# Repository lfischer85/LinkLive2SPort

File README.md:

# LinkLive2SPort
LinkLive to SPort Converter

Contains AVR GCC Files as well as KiCad Files for an Castle Creations LINK LIVE Protocoll to FrSky S.Port Converter.

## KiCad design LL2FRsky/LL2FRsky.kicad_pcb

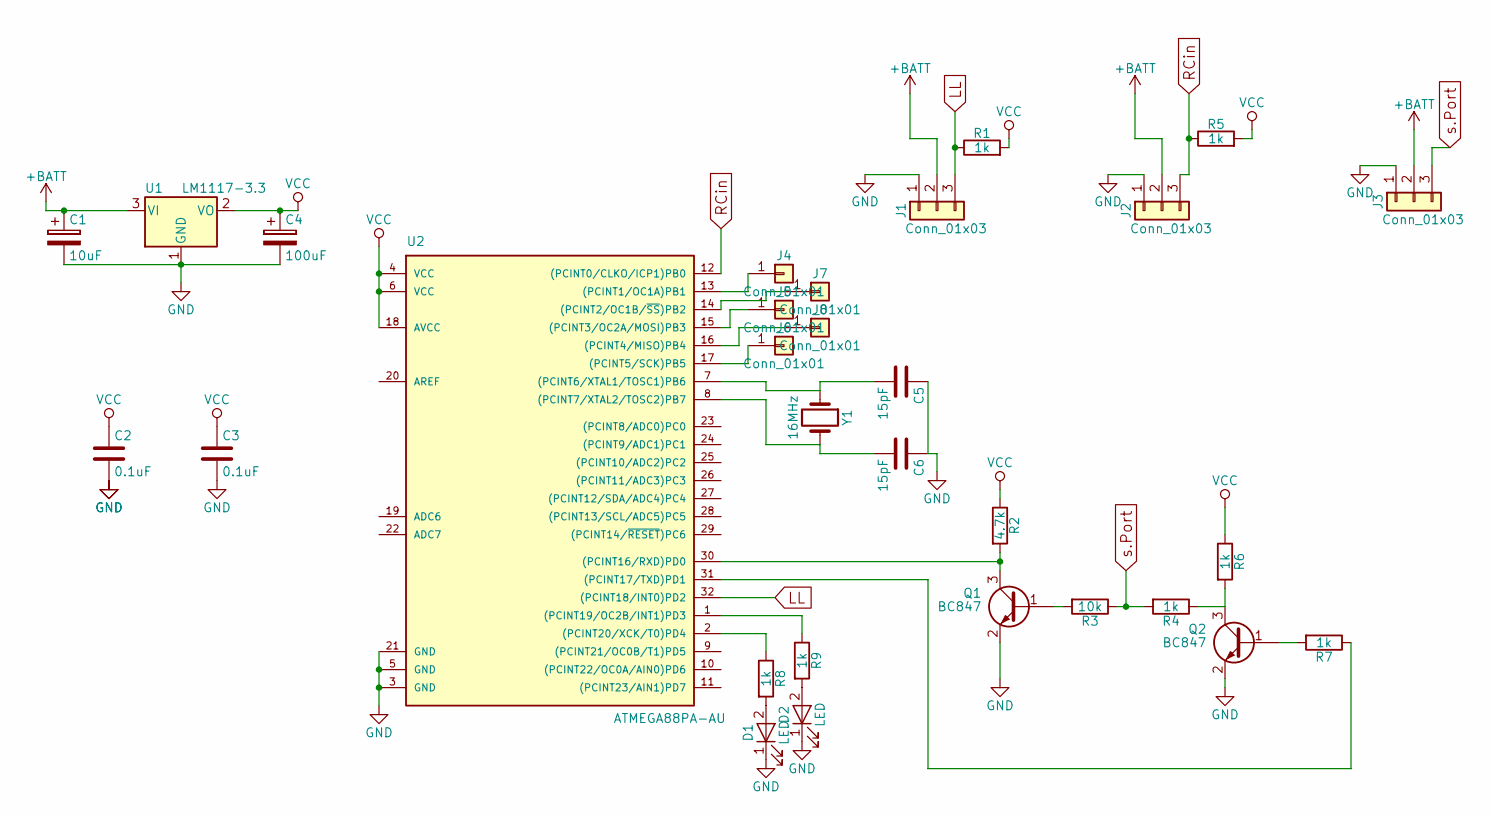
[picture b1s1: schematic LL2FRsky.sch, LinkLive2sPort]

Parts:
C1: 10uF; CP_Tantalum_Case-C_EIA-6032-28_Hand
C2, C3: 0.1uF; C_0805_HandSoldering
C4: 100uF; CP_Tantalum_Case-C_EIA-6032-28_Hand
C5, C6: 15pF; C_0805_HandSoldering
D1, D2: LED; LED_0805_HandSoldering
J1, J2, J3: Conn_01x03; Pin_Header_Straight_1x03_Pitch2.54mm
J4, J5, J6, J7, J8: Conn_01x01; Measurement_Point_Round-SMD-Pad_Small
Q1, Q2: BC847; SOT-23
R1, R4, R5, R6, R7, R8, R9: 1k; R_0805_HandSoldering
R2: 4.7k; R_0805_HandSoldering
R3: 10k; R_0805_HandSoldering
U1: LM1117-3.3; SOT-223-3_TabPin2
U2: ATMEGA88PA-AU; TQFP-32_7x7mm_Pitch0.8mm
Y1: 16MHz; Crystal_SMD_5032-2pin_5.0x3.2mm_HandSoldering

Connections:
+BATT: C1.1, J1.2, J2.2, J3.2, U1.3 (VI)
GND: C1.2, C2.2, C3.2, C4.2, C5.1, C6.1, D1.1 (K), D2.1 (K), J1.1, J2.1, J3.1, Q1.2 (E), Q2.2 (E), U1.1 (GND), U2.3 (GND), U2.5 (GND), U2.21 (GND)
LL: J1.3, R1.1, U2.32 ((PCINT18/INT0)PD2)
unnamed: C5.2, U2.7 ((PCINT6/XTAL1/TOSC1)PB6), Y1.1
unnamed: C6.2, U2.8 ((PCINT7/XTAL2/TOSC2)PB7), Y1.2
unnamed: D1.2 (A), R8.2
unnamed: D2.2 (A), R9.2
unnamed: J4.1, U2.13 ((PCINT1/OC1A)PB1)
unnamed: J5.1, U2.15 ((PCINT3/OC2A/MOSI)PB3)
unnamed: J6.1, U2.17 ((PCINT5/SCK)PB5)
unnamed: J7.1, U2.14 ((PCINT2/OC1B/~SS~)PB2)
unnamed: J8.1, U2.16 ((PCINT4/MISO)PB4)
unnamed: Q1.1 (B), R3.2
unnamed: Q1.3 (C), R2.2, U2.30 ((PCINT16/RXD)PD0)
unnamed: Q2.1 (B), R7.2
unnamed: Q2.3 (C), R4.1, R6.2
unnamed: R7.1, U2.31 ((PCINT17/TXD)PD1)
unnamed: R8.1, U2.2 ((PCINT20/XCK/T0)PD4)
unnamed: R9.1, U2.1 ((PCINT19/OC2B/INT1)PD3)
RCin: J2.3, R5.1, U2.12 ((PCINT0/CLKO/ICP1)PB0)
VCC: C2.1, C3.1, C4.1, R1.2, R2.1, R5.2, R6.1, U1.2 (VO), U2.4 (VCC), U2.6 (VCC), U2.18 (AVCC)
s.Port: J3.3, R3.1, R4.2

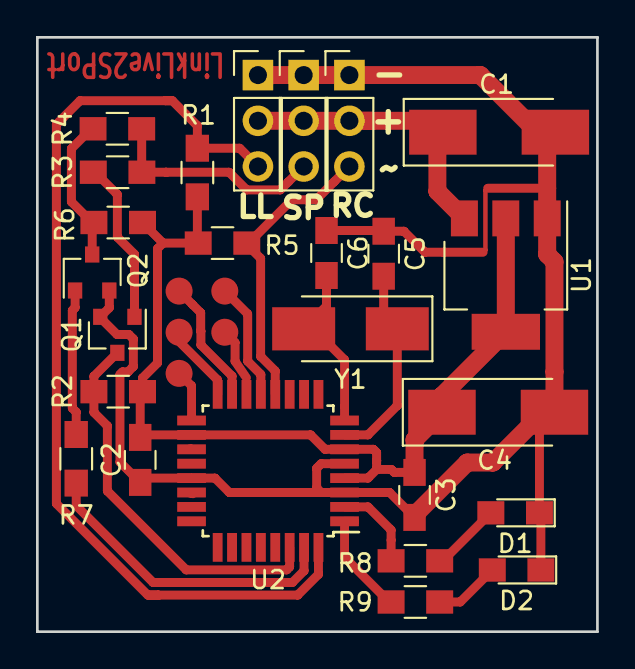
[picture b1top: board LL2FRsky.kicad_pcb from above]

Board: 2 copper layers, 31.1 x 33.0 mm, 30 parts (0 on the bottom side), 22 nets.

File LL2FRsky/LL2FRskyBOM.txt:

Value	Size	DigiKey Article ID
1x	10uF	1206	311-1376-1-ND 
2x	0.1uf	0805	399-1170-1-ND 
1x	100uF	1206	478-8155-1-ND
2x	15pf	0805	
2x	LED		0805	475-1410-1-ND // 475-1278-1-ND
2x	BC847	SOT-23	1727-4853-1-ND 
7x	1k	0805	311-1.0KARCT-ND
1x	10k	0805	311-10KARCT-ND 
1x	4.7k	0805	311-4.70KCRCT-ND 
1x	LM1117-3.3	SOT-223-3	LM1117MPX-3.3/NOPBCT-ND 
1x	ATMEGA88PA-AU	TQFP32	ATMEGA88PA-AU-ND
1x	Crystal	5.0x3.2mm 2pin	1253-1373-1-ND  //  1253-1376-1-ND

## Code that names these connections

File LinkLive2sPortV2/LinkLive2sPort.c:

/*
 * LinkLive2sPort.c
 *
 * Created: 26.12.2015 09:06:38
 *  Author: lfischer85
 
 
 RX		->	PD0
 TX		->	PD1
 LL		->	PD2 (INT0)
 RcIN	->	PB0	(PCInt0)
 
 LED1	->	PD4
 LED2	->	PD3
 
 TODO:
 -better use of calibration data
 -add sensor "power %"
   
 */ 
#include <avr/interrupt.h>
#include <avr/io.h>

#include "sPort.h"
#include "LinkLive.h"

/*  Main  */
int main(void)
{
	uint8_t subSensorCounter;
	uint16_t LED1;
	uint16_t LED2;
	uint8_t rxData, rxLast;
	uint8_t sensorID = 10;

	/* Set led ports as output */
	DDRD |= (1<<PORTD3);
	DDRD |= (1<<PORTD4);
	
	/* Set PortB5 as input with Pullup */
	DDRB &= ~(1<<PORTB5);
	PORTB |= (1<<PORTB5);
	

	LLinit();
	sPortInit();

	/*  Init Global  */
	sei();			// Enable all Interrupts
	
	// set SensorID = 11 if PB5 shorted to GND
	if( !(PINB & (1<<PINB5)) )
	{
		sensorID = 11;
	}
	
    while(1)
    {
		if (LLPacketReadyFlag)
		{
			// LinkLive data received
			LED1 = 30000;
		}
		
		if(sPortReadByteReady())
		{		
			rxData=sPortReadByte();
			if ( (rxData==sPortSensorID(sensorID)) && (rxLast==SPORT_HEADER_REQUEST))
			{
				// SPORT data received
				LED2 = 30000;
			}
			
			if ( (rxData==sPortSensorID(sensorID)) && (rxLast==SPORT_HEADER_REQUEST) && LLPacketReadyFlag)
			{
				switch(subSensorCounter)
				{
					case 0:
					sPortSendPacket(VFAS_FIRST_ID,LLValueArray[1]/10);		// Voltage
					break;
				
					case 1:
					sPortSendPacket(VFAS_FIRST_ID+1,LLValueArray[2]/10);	// Ripple Voltage
					break;
				
					case 2:
					sPortSendPacket(CURR_FIRST_ID,LLValueArray[3]/100);		// Current
					break;
				
					case 3:
					sPortSendPacket(VFAS_FIRST_ID+2,LLValueArray[7]/10);	// BEC Voltage
					break;
				
					case 4:
					sPortSendPacket(CURR_FIRST_ID+1,LLValueArray[8]/100);	// BEC Current
					break;
				
					case 5:
					sPortSendPacket(T1_FIRST_ID,LLValueArray[9]);			// Temperature
					break;
				
					case 6:
					sPortSendPacket(RPM_FIRST_ID,LLValueArray[6]);			// Electrical RPM
					break;
				
				}	
				if (subSensorCounter == 6)
				{
					subSensorCounter = 0;
					LLPacketReadyFlag = 0; // only send data again when new data available
				}
				else
				{
					subSensorCounter++;
				}
			}  
			rxLast = rxData;
		}
		// check / set led status
		if (LED1 > 0)
		{
			LED1 --;
			PORTD |= (1<<PIND3);
		}
		else
		{
			PORTD &= ~(1<<PIND3);
		}			
		if (LED2 > 0)
		{
			LED2 --;
			PORTD |= (1<<PIND4);
		}
		else
		{
			PORTD &= ~(1<<PIND4);
		}
    }
}
